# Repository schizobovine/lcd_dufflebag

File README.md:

lcd_dufflebag
=============

Variation on the common LCD "backpack" design. Instead of using an IO expander or full blown ATMega, however, this design uses an ATTiny84 to drive the LCD, with just enough pins left over to be an I2C slave. Can control RGB LCDs via an optional WS2811 chip or monochrome displays via a simple BJT.

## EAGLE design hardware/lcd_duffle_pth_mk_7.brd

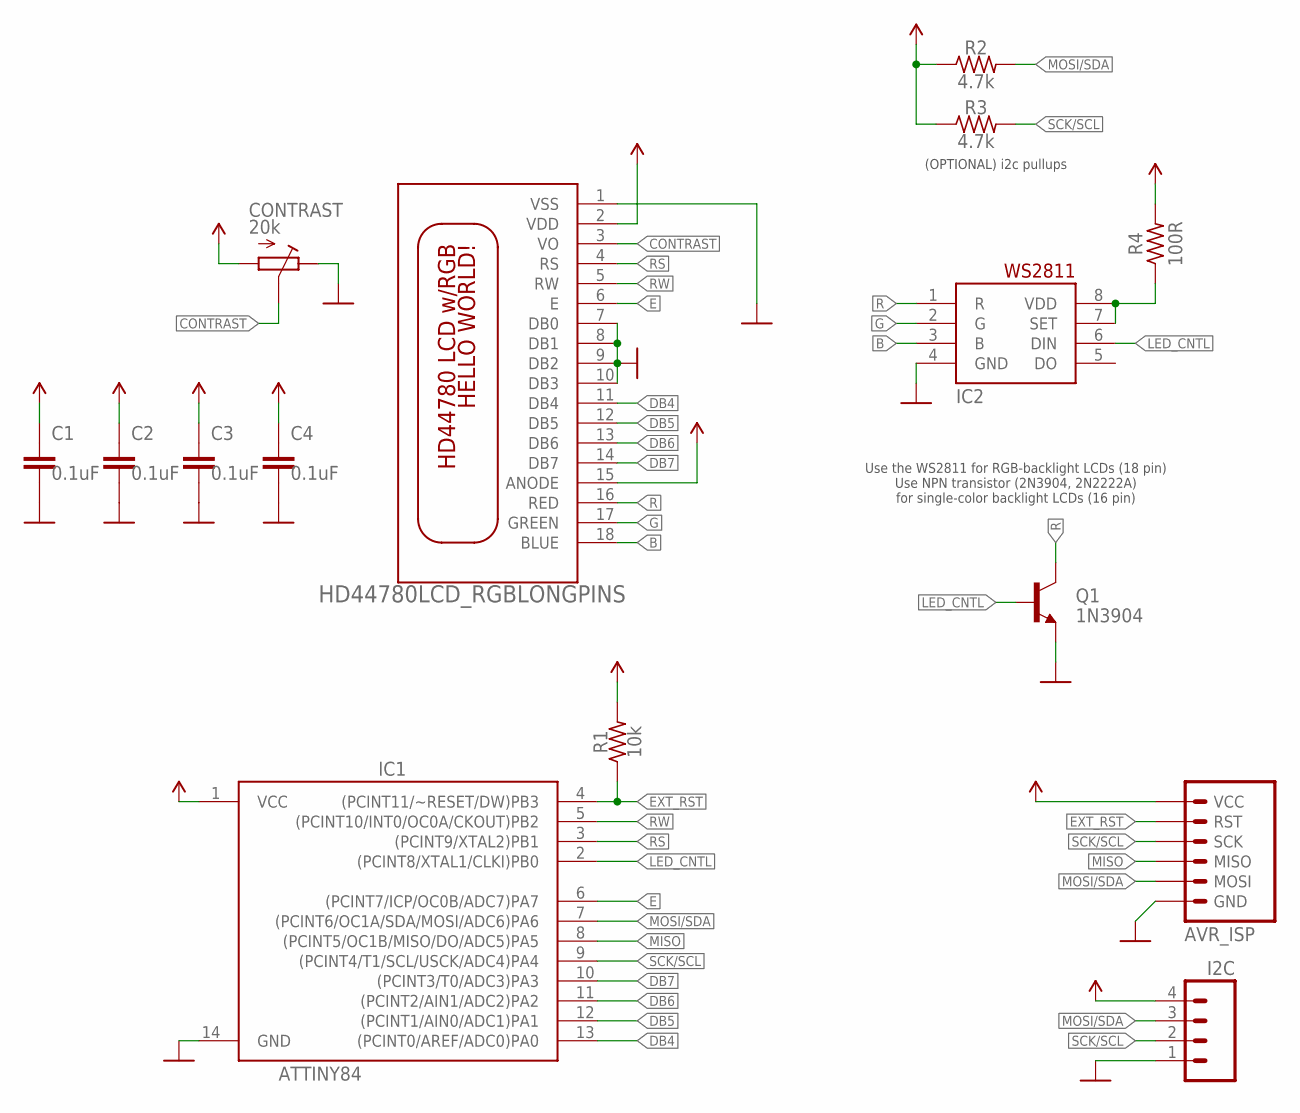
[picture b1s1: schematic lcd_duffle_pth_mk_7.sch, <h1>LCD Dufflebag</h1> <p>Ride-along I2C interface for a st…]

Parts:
AVR_ISP: AVR_MINI_PROGJST-XH-RA-PTH; AVR_MINI_PROG_JST_XH_RA
C1, C2, C3, C4: 0.1uF; C025-024X044
CONTRAST: 20k; POT-THUMBWHEEL
I2C: M04JST_XH_RA; JST-4-XH-RA-PTH
IC1: ATTINY84; DIL14
IC2: WS2811; SO08-SKINNYPADS
Q1: 1N3904; TO-92-AMMO
R1: 10k; RESISTOR-AXIAL-PTH-5.08MM
R2, R3: 4.7k; RESISTOR-AXIAL-PTH-5.08MM
R4: 100R; RESISTOR-AXIAL-PTH-5.08MM
U$1: HD44780LCD_RGBLONGPINS; LCD1602-RGB-CENTERED

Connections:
5V: AVR_ISP.2 (VCC), C1.2, C2.2, C3.2, C4.2, CONTRAST.1 (A), I2C.4, IC1.1 (VCC), R1.P$2 (2), R2.P$1 (1), R3.P$1 (1), R4.P$2 (2), U$1.2 (VDD), U$1.15 (ANODE)
B: IC2.3 (B), U$1.18 (BLUE)
CONTRAST: CONTRAST.2 (S), CONTRAST.2@1 (S), U$1.3 (VO)
DB4: IC1.13 ((PCINT0/AREF/ADC0)PA0), U$1.11 (DB4)
DB5: IC1.12 ((PCINT1/AIN0/ADC1)PA1), U$1.12 (DB5)
DB6: IC1.11 ((PCINT2/AIN1/ADC2)PA2), U$1.13 (DB6)
DB7: IC1.10 ((PCINT3/T0/ADC3)PA3), U$1.14 (DB7)
E: IC1.6 ((PCINT7/ICP/OC0B/ADC7)PA7), U$1.6 (E)
EXT_RST: AVR_ISP.5 (RST), IC1.4 ((PCINT11/~RESET/DW)PB3), R1.P$1 (1)
G: IC2.2 (G), U$1.17 (GREEN)
GND: AVR_ISP.6 (GND), C1.1, C2.1, C3.1, C4.1, CONTRAST.3 (E), I2C.1, IC1.14 (GND), IC2.4 (GND), Q1.1 (E), U$1.1 (VSS), U$1.7 (DB0), U$1.8 (DB1), U$1.9 (DB2), U$1.10 (DB3)
LED_CNTL: IC1.2 ((PCINT8/XTAL1/CLKI)PB0), IC2.6 (DIN), Q1.2 (B)
MISO: AVR_ISP.1 (MISO), IC1.8 ((PCINT5/OC1B/MISO/DO/ADC5)PA5)
MOSI/SDA: AVR_ISP.4 (MOSI), I2C.3, IC1.7 ((PCINT6/OC1A/SDA/MOSI/ADC6)PA6), R2.P$2 (2)
unnamed: IC2.7 (SET), IC2.8 (VDD), R4.P$1 (1)
R: IC2.1 (R), Q1.3 (C), U$1.16 (RED)
RS: IC1.3 ((PCINT9/XTAL2)PB1), U$1.4 (RS)
RW: IC1.5 ((PCINT10/INT0/OC0A/CKOUT)PB2), U$1.5 (RW)
SCK/SCL: AVR_ISP.3 (SCK), I2C.2, IC1.9 ((PCINT4/T1/SCL/USCK/ADC4)PA4), R3.P$2 (2)

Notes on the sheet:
Use the WS2811 for RGB-backlight LCDs (18 pin) Use NPN transistor (2N3904, 2N2222A) for single-color backlight LCDs (16 pin)
(OPTIONAL) i2c pullups

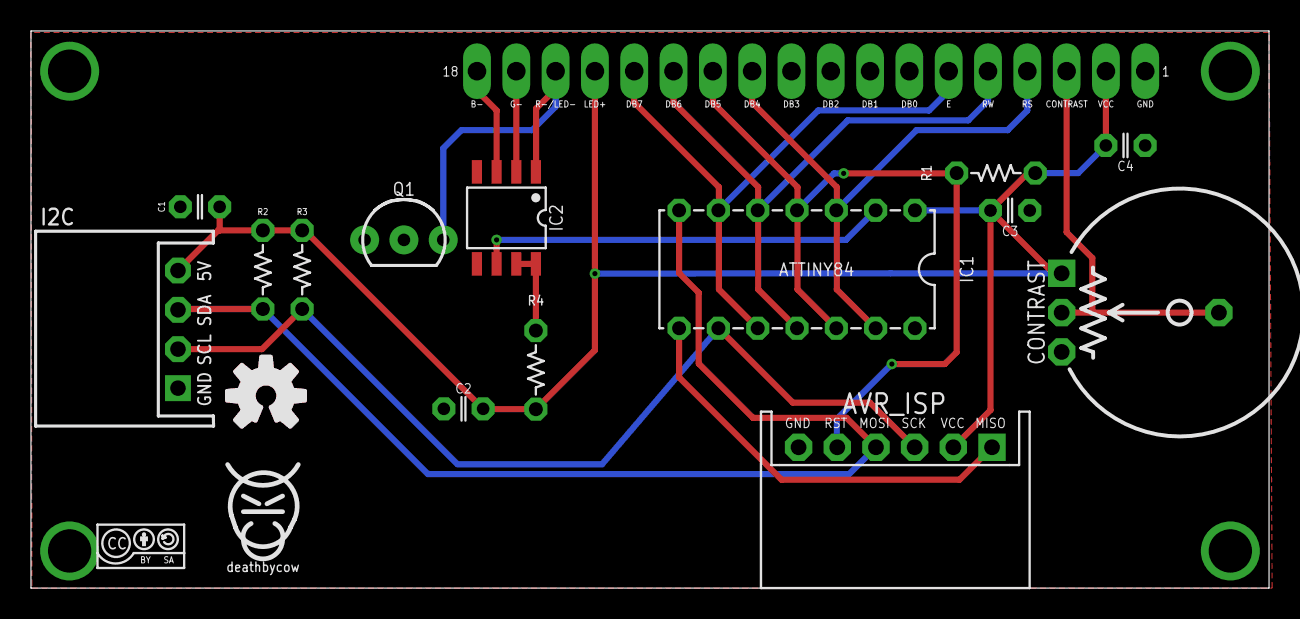
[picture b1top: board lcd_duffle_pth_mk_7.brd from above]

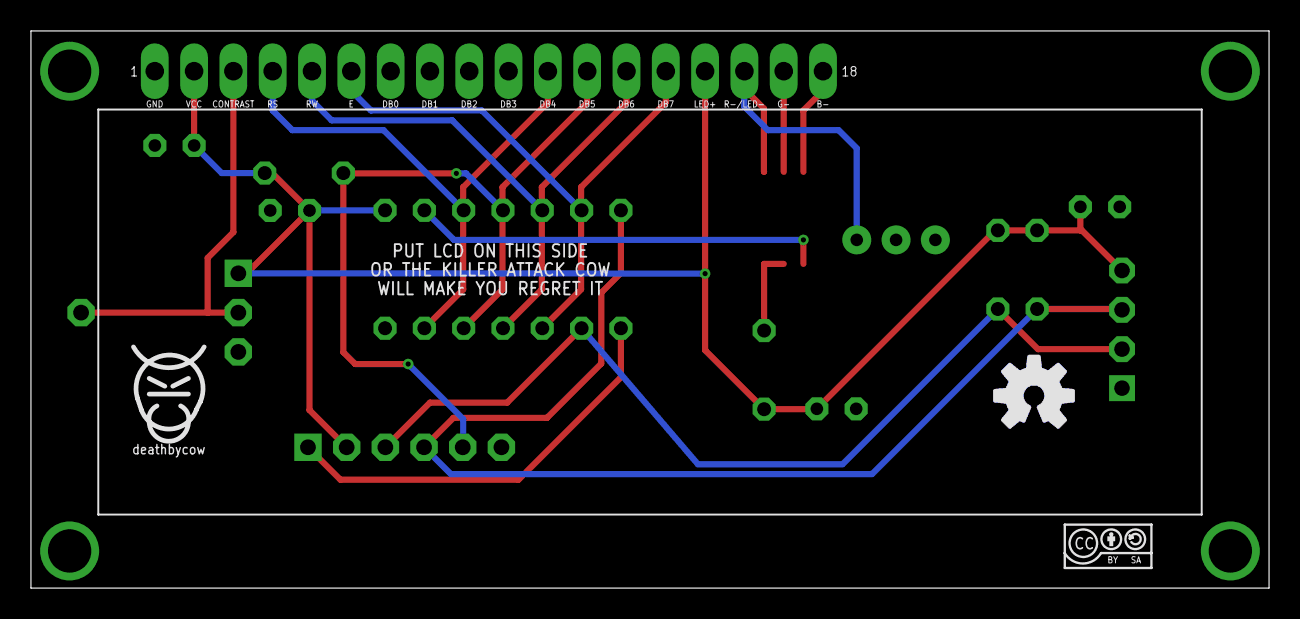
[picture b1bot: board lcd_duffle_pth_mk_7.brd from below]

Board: 2 copper layers, 80.0 x 36.0 mm, 21 parts (5 on the bottom side), 19 nets.

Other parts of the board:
U$2, U$3: COW_SMALL
U$4, U$6: CC-BY-SA-4.0-NO-URL
U$5: OSHWLOGO_TOP_0.2_A
U$7: OSHWLOGO_BOT_0.2_A

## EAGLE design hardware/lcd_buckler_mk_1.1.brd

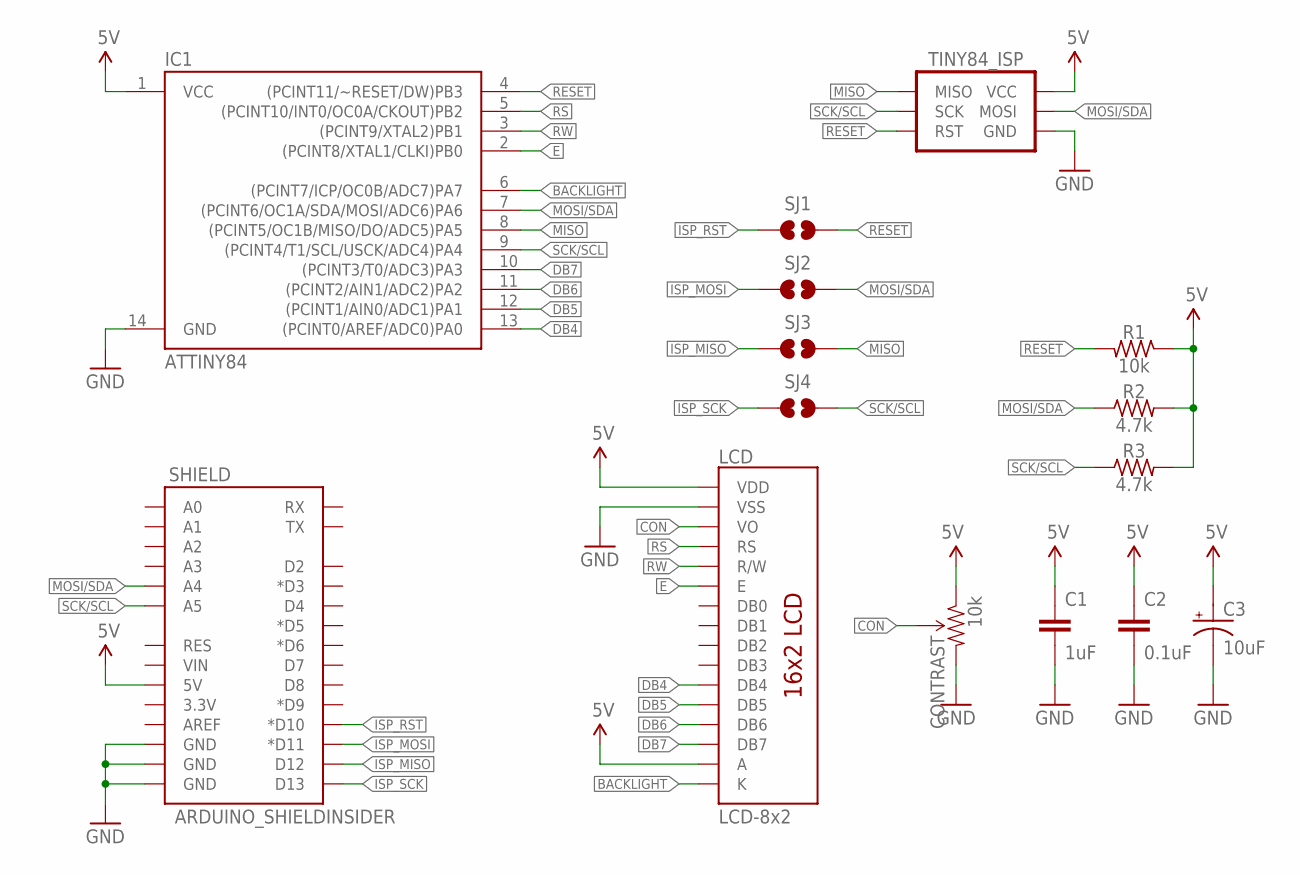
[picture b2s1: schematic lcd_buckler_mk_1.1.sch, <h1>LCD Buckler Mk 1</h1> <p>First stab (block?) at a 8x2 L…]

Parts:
C1: 1uF; C025-024X044
C2: 0.1uF; C025-024X044
C3: 10uF; E2,5-5
CONTRAST: 10k; TRIM_POT_PTH
IC1: ATTINY84; DIL14
LCD: LCD-8x2; LCD-8X2
R1: 10k; RESISTOR-AXIAL-PTH-7.62MM
R2, R3: 4.7k; RESISTOR-AXIAL-PTH-7.62MM
SHIELD: ARDUINO_SHIELDINSIDER; ARDUINO_SHIELD_NOOUTLINE_INSIDE
SJ1, SJ2, SJ3, SJ4: JUMPER-PAD-2-NO; PAD-JUMPER-2-NO_NO_SILK
TINY84_ISP: AVR_SPI_PRG_6PTH; 2X3

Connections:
5V: C1.1, C2.1, C3.+, CONTRAST.1 (CCW), IC1.1 (VCC), LCD.2 (VDD), LCD.15 (A), R1.P$1 (1), R2.P$2 (2), R3.P$2 (2), SHIELD.5V, TINY84_ISP.2 (VCC)
BACKLIGHT: IC1.6 ((PCINT7/ICP/OC0B/ADC7)PA7), LCD.16 (K)
CON: CONTRAST.2 (WIPER), LCD.3 (VO)
DB4: IC1.13 ((PCINT0/AREF/ADC0)PA0), LCD.11 (DB4)
DB5: IC1.12 ((PCINT1/AIN0/ADC1)PA1), LCD.12 (DB5)
DB6: IC1.11 ((PCINT2/AIN1/ADC2)PA2), LCD.13 (DB6)
DB7: IC1.10 ((PCINT3/T0/ADC3)PA3), LCD.14 (DB7)
E: IC1.2 ((PCINT8/XTAL1/CLKI)PB0), LCD.6 (E)
GND: C1.2, C2.2, C3.-, CONTRAST.3 (CW), IC1.14 (GND), LCD.1 (VSS), SHIELD.GND@0 (GND), SHIELD.GND@1 (GND), SHIELD.GND@2 (GND), TINY84_ISP.6 (GND)
ISP_MISO: SHIELD.D12, SJ3.1
ISP_MOSI: SHIELD.D11 (*D11), SJ2.1
ISP_RST: SHIELD.D10 (*D10), SJ1.1
ISP_SCK: SHIELD.D13, SJ4.1
MISO: IC1.8 ((PCINT5/OC1B/MISO/DO/ADC5)PA5), SJ3.2, TINY84_ISP.1 (MISO)
MOSI/SDA: IC1.7 ((PCINT6/OC1A/SDA/MOSI/ADC6)PA6), R2.P$1 (1), SHIELD.A4, SJ2.2, TINY84_ISP.4 (MOSI)
RESET: IC1.4 ((PCINT11/~RESET/DW)PB3), R1.P$2 (2), SJ1.2, TINY84_ISP.5 (RST)
RS: IC1.5 ((PCINT10/INT0/OC0A/CKOUT)PB2), LCD.4 (RS)
RW: IC1.3 ((PCINT9/XTAL2)PB1), LCD.5 (R/W)
SCK/SCL: IC1.9 ((PCINT4/T1/SCL/USCK/ADC4)PA4), R3.P$1 (1), SHIELD.A5, SJ4.2, TINY84_ISP.3 (SCK)

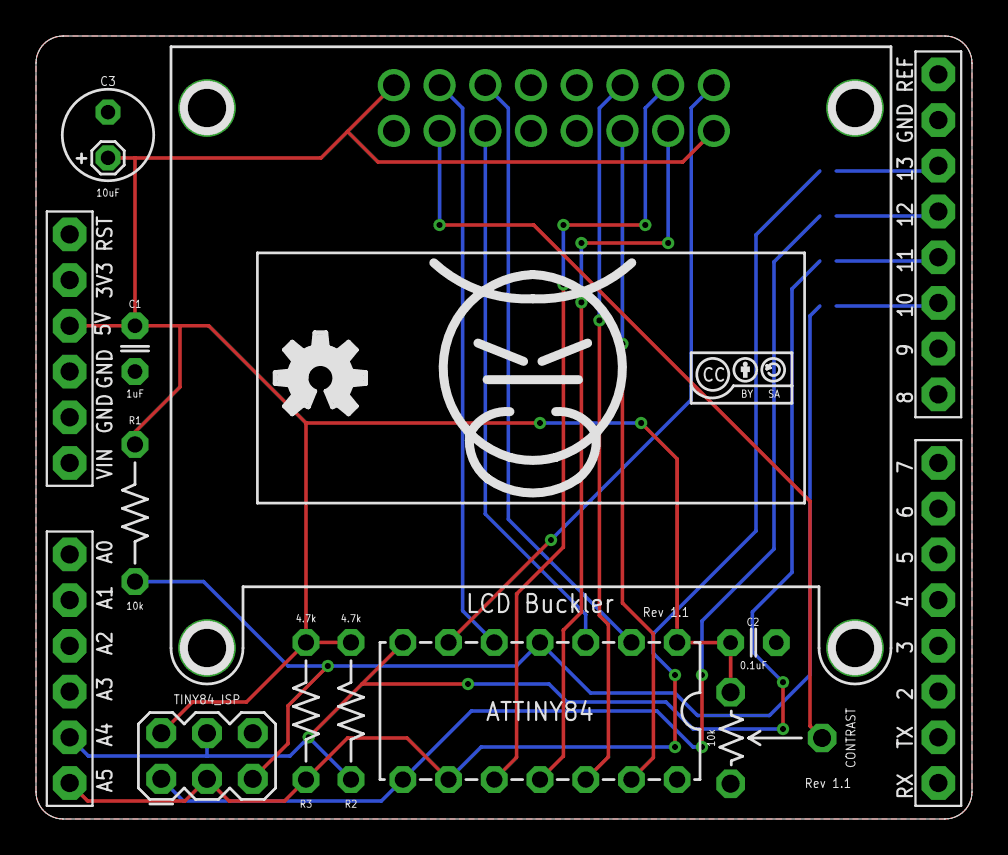
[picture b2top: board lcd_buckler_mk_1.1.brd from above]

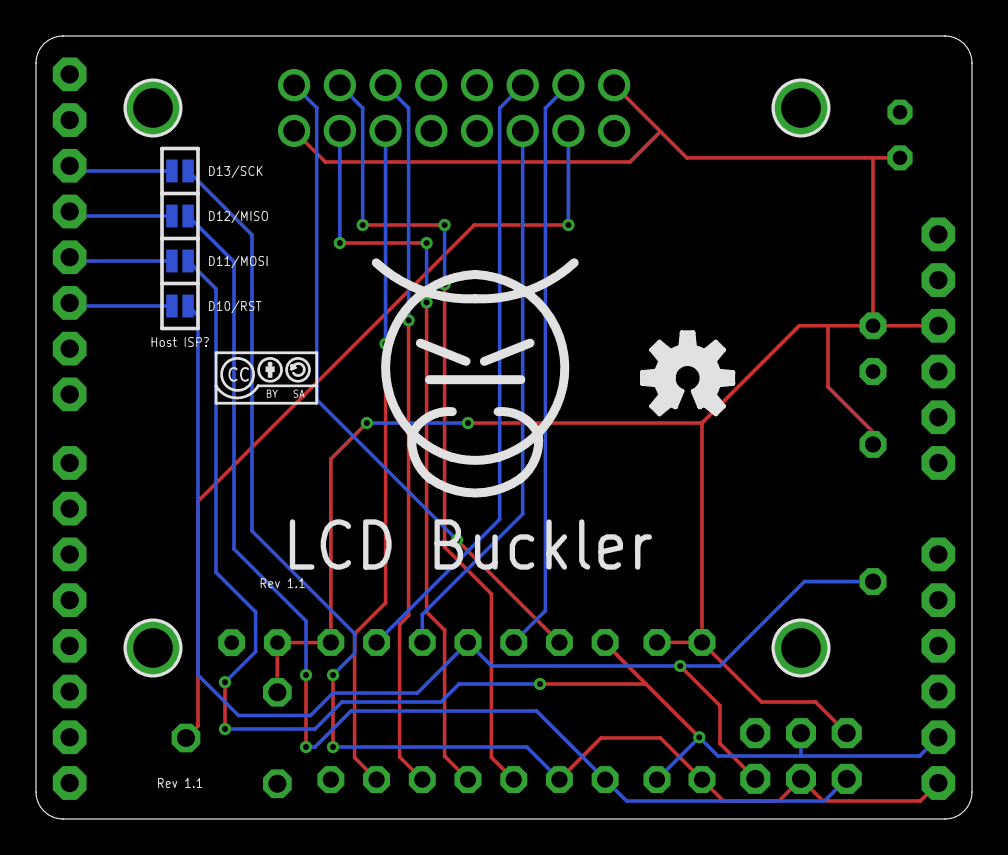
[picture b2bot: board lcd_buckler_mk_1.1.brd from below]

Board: 2 copper layers, 52.0 x 43.5 mm, 21 parts (7 on the bottom side), 19 nets.

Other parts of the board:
U$1, U$2: COW
U$3, U$4: CC-BY-SA-4.0-NO-URL
U$5, U$6: OSHWLOGO_SILKONLY

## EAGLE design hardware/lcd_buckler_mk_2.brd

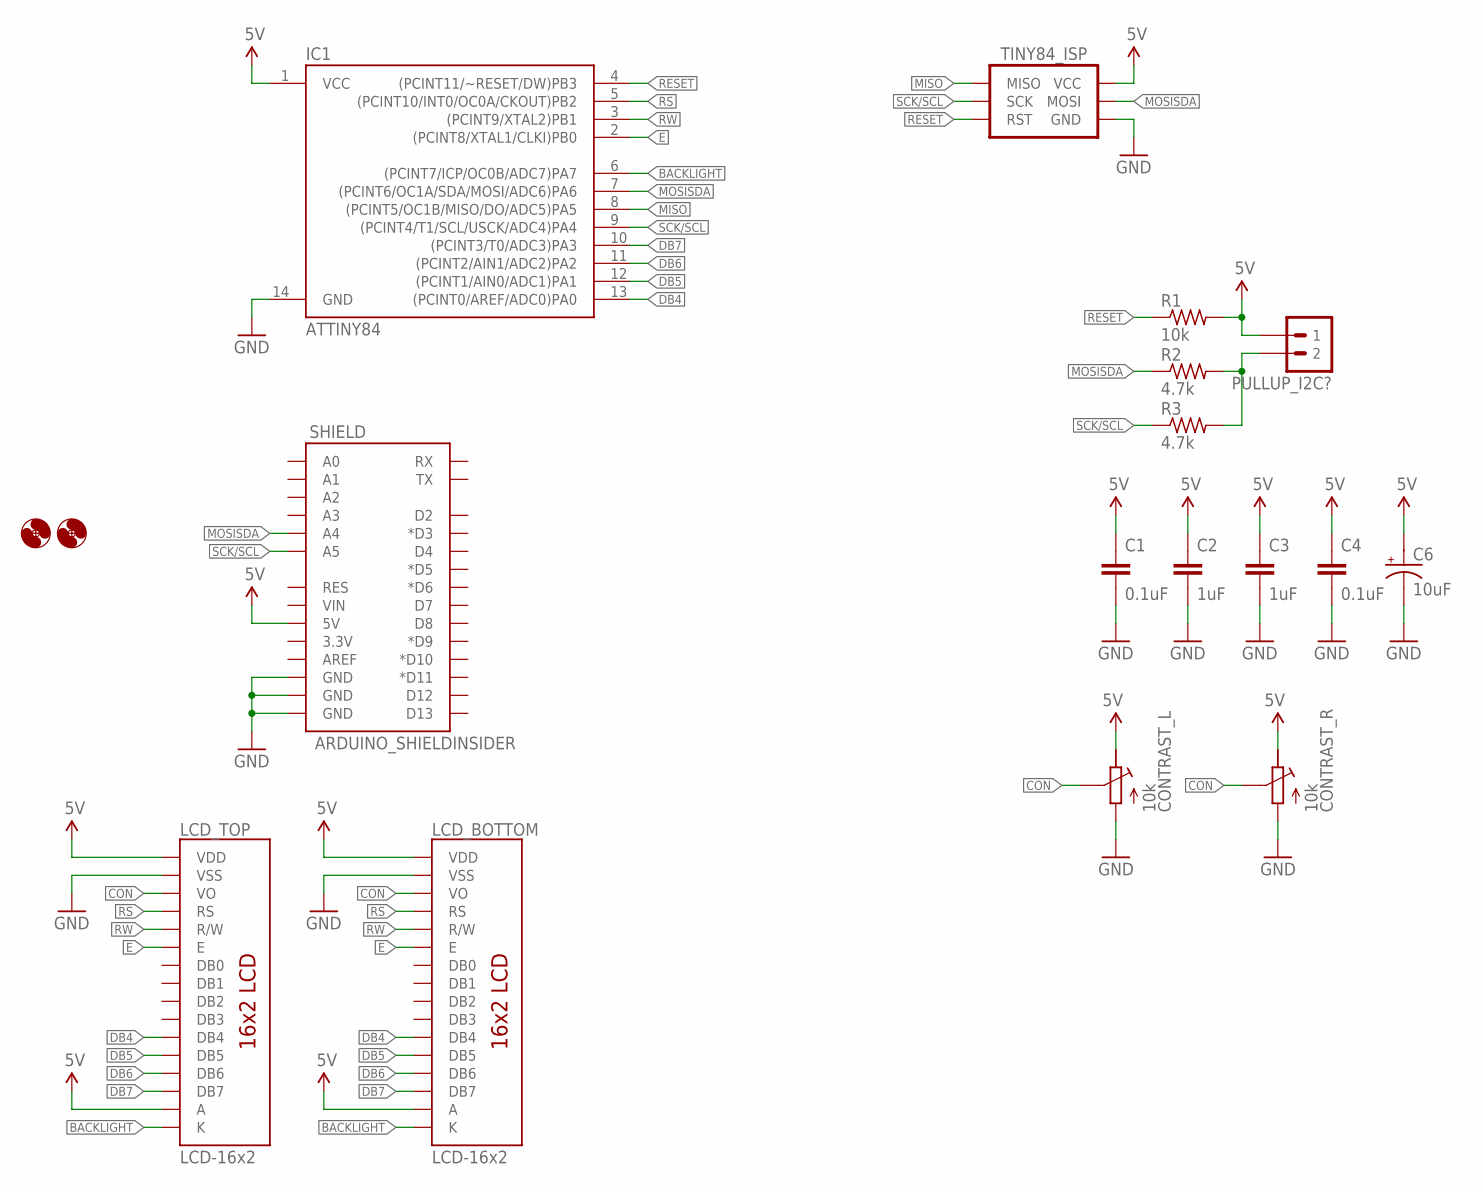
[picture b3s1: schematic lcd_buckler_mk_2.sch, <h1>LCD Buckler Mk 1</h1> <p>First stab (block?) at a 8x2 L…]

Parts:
C1: 0.1uF; C0805
C2, C3: 1uF; C025-024X044
C4: 0.1uF; C025-024X044
C6: 10uF; E2,5-5
CONTRAST_L: 10k; POT-THUMBWHEEL
CONTRAST_R: 10k; POT-THUMBWHEEL
H1, H2: HOLE#2; HOLE-#2
IC1: ATTINY84; SO14
LCD_BOTTOM: LCD-16x2; LCD-16X2-PINS-ONLY
LCD_TOP: LCD-16x2; LCD-16X2-PINS-ONLY
PULLUP_I2C?: M02PTH; 1X02
R1: 10k; R0805
R2, R3: 4.7k; RESISTOR-AXIAL-PTH-7.68MM
SHIELD: ARDUINO_SHIELDINSIDER; ARDUINO_SHIELD_NOOUTLINE_INSIDE
TINY84_ISP: AVR_SPI_PRG_6PTH; 2X3

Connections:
5V: C1.1, C2.1, C3.1, C4.1, C6.+, CONTRAST_L.3 (E), CONTRAST_R.3 (E), IC1.1 (VCC), LCD_BOTTOM.2 (VDD), LCD_BOTTOM.15 (A), LCD_TOP.2 (VDD), LCD_TOP.15 (A), PULLUP_I2C?.1, R1.2, SHIELD.5V, TINY84_ISP.2 (VCC)
BACKLIGHT: IC1.6 ((PCINT7/ICP/OC0B/ADC7)PA7), LCD_BOTTOM.16 (K), LCD_TOP.16 (K)
CON: CONTRAST_L.2 (S), CONTRAST_L.2@1 (S), CONTRAST_R.2 (S), CONTRAST_R.2@1 (S), LCD_BOTTOM.3 (VO), LCD_TOP.3 (VO)
DB4: IC1.13 ((PCINT0/AREF/ADC0)PA0), LCD_BOTTOM.11 (DB4), LCD_TOP.11 (DB4)
DB5: IC1.12 ((PCINT1/AIN0/ADC1)PA1), LCD_BOTTOM.12 (DB5), LCD_TOP.12 (DB5)
DB6: IC1.11 ((PCINT2/AIN1/ADC2)PA2), LCD_BOTTOM.13 (DB6), LCD_TOP.13 (DB6)
DB7: IC1.10 ((PCINT3/T0/ADC3)PA3), LCD_BOTTOM.14 (DB7), LCD_TOP.14 (DB7)
E: IC1.2 ((PCINT8/XTAL1/CLKI)PB0), LCD_BOTTOM.6 (E), LCD_TOP.6 (E)
GND: C1.2, C2.2, C3.2, C4.2, C6.-, CONTRAST_L.1 (A), CONTRAST_R.1 (A), IC1.14 (GND), LCD_BOTTOM.1 (VSS), LCD_TOP.1 (VSS), SHIELD.GND@0 (GND), SHIELD.GND@1 (GND), SHIELD.GND@2 (GND), TINY84_ISP.6 (GND)
MISO: IC1.8 ((PCINT5/OC1B/MISO/DO/ADC5)PA5), TINY84_ISP.1 (MISO)
MOSISDA: IC1.7 ((PCINT6/OC1A/SDA/MOSI/ADC6)PA6), R2.P$1 (1), SHIELD.A4, TINY84_ISP.4 (MOSI)
unnamed: PULLUP_I2C?.2, R2.P$2 (2), R3.P$2 (2)
RESET: IC1.4 ((PCINT11/~RESET/DW)PB3), R1.1, TINY84_ISP.5 (RST)
RS: IC1.5 ((PCINT10/INT0/OC0A/CKOUT)PB2), LCD_BOTTOM.4 (RS), LCD_TOP.4 (RS)
RW: IC1.3 ((PCINT9/XTAL2)PB1), LCD_BOTTOM.5 (R/W), LCD_TOP.5 (R/W)
SCK/SCL: IC1.9 ((PCINT4/T1/SCL/USCK/ADC4)PA4), R3.P$1 (1), SHIELD.A5, TINY84_ISP.3 (SCK)

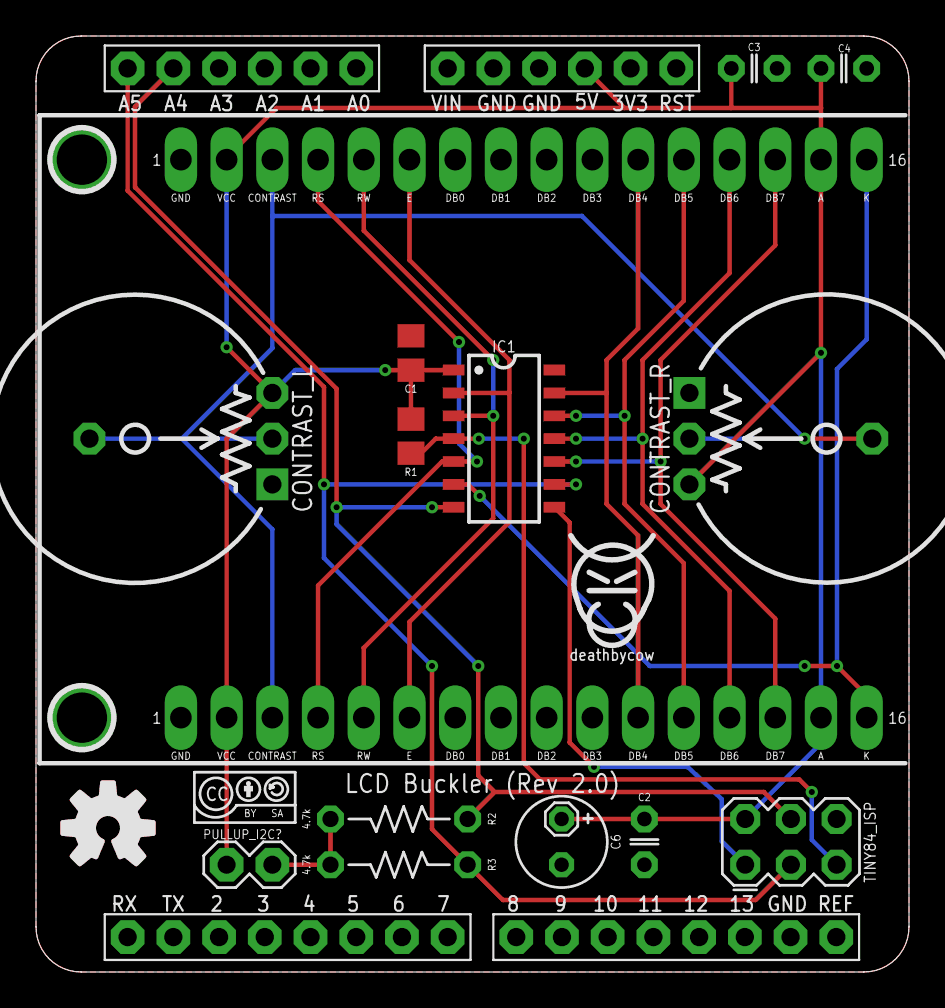
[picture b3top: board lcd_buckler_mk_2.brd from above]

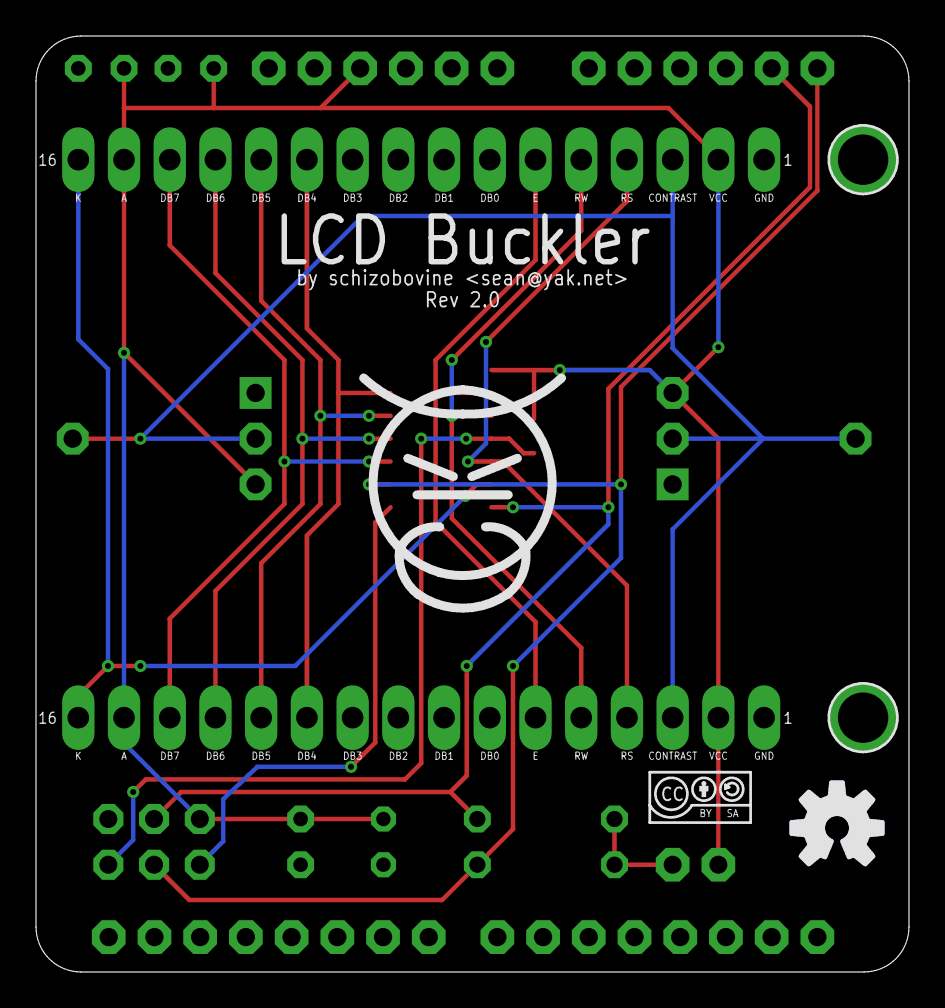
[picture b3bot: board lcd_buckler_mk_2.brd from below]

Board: 2 copper layers, 48.5 x 52.0 mm, 24 parts (2 on the bottom side), 16 nets.

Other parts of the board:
U$1: COW
U$2: COW_SMALL
U$3, U$4: CC-BY-SA-4.0-NO-URL
U$5: OSHWLOGO_TOP_0.2_A
U$6: OSHWLOGO_BOT_0.2_A

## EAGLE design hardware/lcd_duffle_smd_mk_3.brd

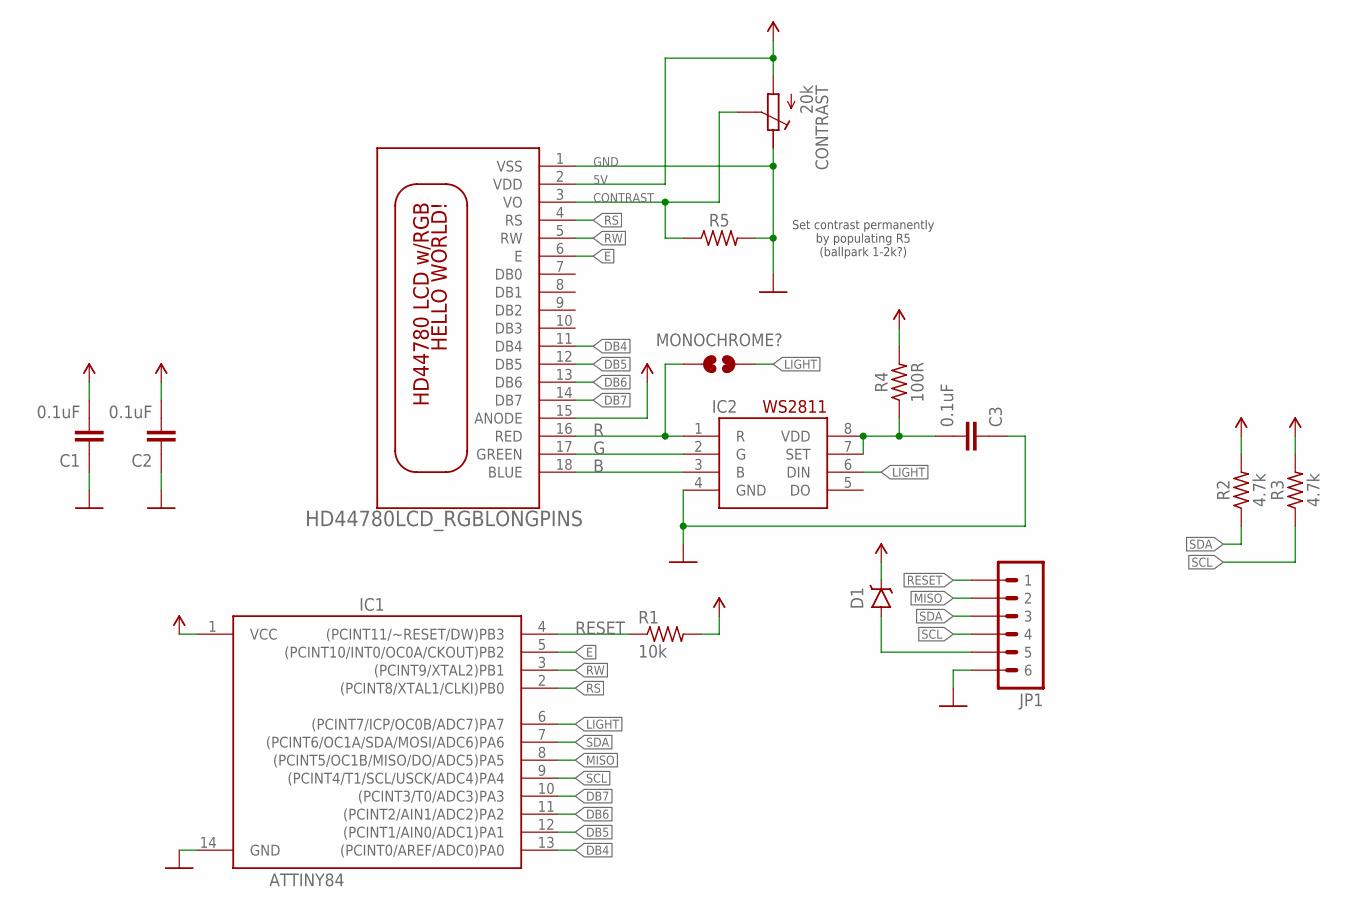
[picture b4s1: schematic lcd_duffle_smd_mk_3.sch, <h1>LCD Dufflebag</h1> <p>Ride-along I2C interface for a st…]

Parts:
C1, C2, C3: 0.1uF; C0805
CONTRAST: 20k; RTRIM3314Z-SIDE
D1: MBRA140; SMA-DIODE
IC1: ATTINY84; SO14
IC2: WS2811; SO08-SKINNYPADS
JP1: M06SMD; 1X06-SMD
MONOCHROME?: JUMPER-PAD-2-NOYES_SILK; PAD-JUMPER-2-NO_YES_SILK
R1: 10k; R0805
R2, R3: 4.7k; R0805
R4: 100R; R0805
R5: RESISTORR0805; R0805
U$1: HD44780LCD_RGBLONGPINS; LCD1602-RGB-CENTERED

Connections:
5V: C1.2, C2.2, CONTRAST.1 (A), D1.C, IC1.1 (VCC), R1.2, R2.2, R3.2, R4.2, U$1.2 (VDD), U$1.15 (ANODE)
B: IC2.3 (B), U$1.18 (BLUE)
CONTRAST: CONTRAST.2 (S), R5.1, U$1.3 (VO)
DB4: IC1.13 ((PCINT0/AREF/ADC0)PA0), U$1.11 (DB4)
DB5: IC1.12 ((PCINT1/AIN0/ADC1)PA1), U$1.12 (DB5)
DB6: IC1.11 ((PCINT2/AIN1/ADC2)PA2), U$1.13 (DB6)
DB7: IC1.10 ((PCINT3/T0/ADC3)PA3), U$1.14 (DB7)
E: IC1.5 ((PCINT10/INT0/OC0A/CKOUT)PB2), U$1.6 (E)
G: IC2.2 (G), U$1.17 (GREEN)
GND: C1.1, C2.1, C3.1, CONTRAST.3 (E), IC1.14 (GND), IC2.4 (GND), JP1.6, R5.2, U$1.1 (VSS)
LIGHT: IC1.6 ((PCINT7/ICP/OC0B/ADC7)PA7), IC2.6 (DIN), MONOCHROME?.2
MISO: IC1.8 ((PCINT5/OC1B/MISO/DO/ADC5)PA5), JP1.2
unnamed: D1.A, JP1.5
unnamed: C3.2, IC2.7 (SET), IC2.8 (VDD), R4.1
R: IC2.1 (R), MONOCHROME?.1, U$1.16 (RED)
RESET: IC1.4 ((PCINT11/~RESET/DW)PB3), JP1.1, R1.1
RS: IC1.2 ((PCINT8/XTAL1/CLKI)PB0), U$1.4 (RS)
RW: IC1.3 ((PCINT9/XTAL2)PB1), U$1.5 (RW)
SCL: IC1.9 ((PCINT4/T1/SCL/USCK/ADC4)PA4), JP1.4, R3.1
SDA: IC1.7 ((PCINT6/OC1A/SDA/MOSI/ADC6)PA6), JP1.3, R2.1

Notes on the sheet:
Set contrast permanently by populating R5 (ballpark 1-2k?)

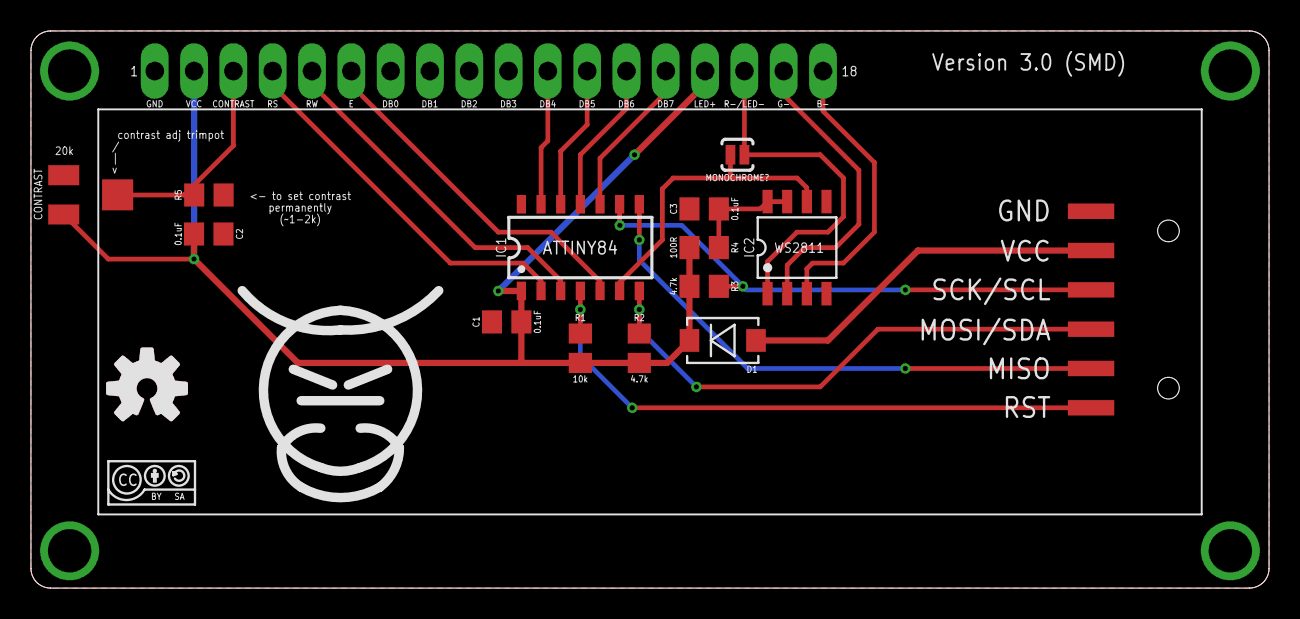
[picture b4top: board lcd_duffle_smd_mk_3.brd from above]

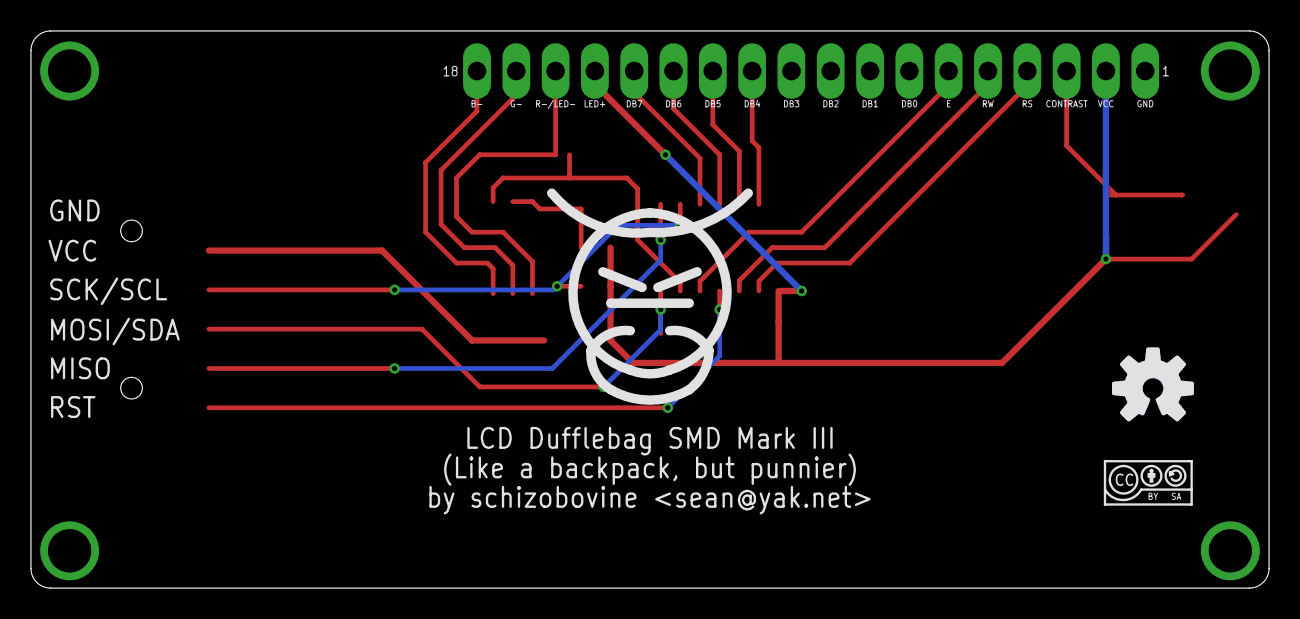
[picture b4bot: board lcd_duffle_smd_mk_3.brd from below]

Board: 2 copper layers, 80.0 x 36.0 mm, 21 parts (2 on the bottom side), 20 nets.

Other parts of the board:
U$2, U$3: COW
U$4, U$5: CC-BY-SA-4.0-NO-URL
U$6: OSHWLOGO_TOP_0.2_A
U$7: OSHWLOGO_BOT_0.2_A

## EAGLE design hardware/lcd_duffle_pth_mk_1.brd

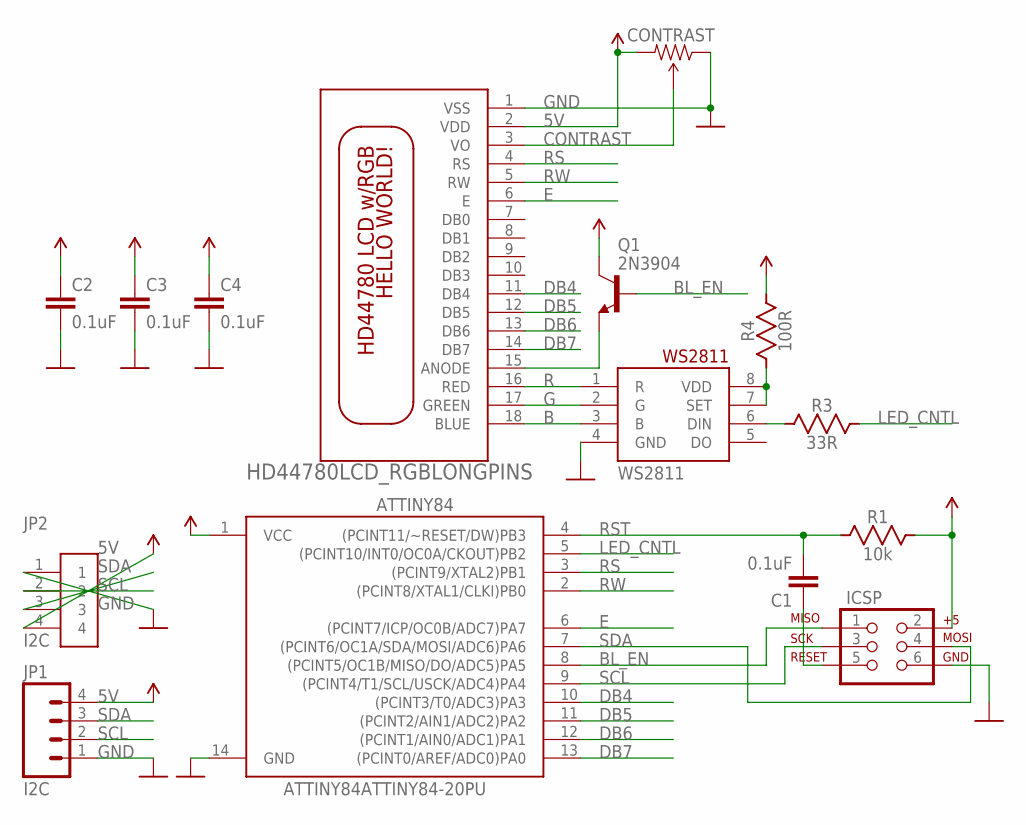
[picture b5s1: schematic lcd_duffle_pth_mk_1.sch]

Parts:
ATTINY84: ATTINY84ATTINY84-20PU; DIL14
C1, C2, C3, C4: 0.1uF; C025-024X044
CONTRAST: TRIMPOT3362U-2; 3362U-2
ICSP: AVR_SPI_PRG_6PTH; 2X3
JP1: I2C; MOLEX-1X4
JP2: I2C; 1X04-BIG
Q1: 2N3904; TO-92-AMMO
R1: 10k; AXIAL-PTH-5.08MM
R3: 33R; AXIAL-PTH-5.08MM
R4: 100R; AXIAL-PTH-5.08MM
U$1: HD44780LCD_RGBLONGPINS; LCD1602-RGB
WS2811: WS2811-SOP8; SO08-SKINNYPADS

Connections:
5V: ATTINY84.1 (VCC), C2.2, C3.2, C4.2, CONTRAST.3 (CW), ICSP.2, JP1.4, JP2.4, Q1.3 (C), R1.P$1 (2), R4.P$1 (2), U$1.2 (VDD)
B: U$1.18 (BLUE), WS2811.3 (B)
BL_EN: ATTINY84.8 ((PCINT5/OC1B/MISO/DO/ADC5)PA5), ICSP.1, Q1.2 (B)
CONTRAST: CONTRAST.2 (WIPER), U$1.3 (VO)
DB4: ATTINY84.10 ((PCINT3/T0/ADC3)PA3), U$1.11 (DB4)
DB5: ATTINY84.11 ((PCINT2/AIN1/ADC2)PA2), U$1.12 (DB5)
DB6: ATTINY84.12 ((PCINT1/AIN0/ADC1)PA1), U$1.13 (DB6)
DB7: ATTINY84.13 ((PCINT0/AREF/ADC0)PA0), U$1.14 (DB7)
E: ATTINY84.6 ((PCINT7/ICP/OC0B/ADC7)PA7), U$1.6 (E)
G: U$1.17 (GREEN), WS2811.2 (G)
GND: ATTINY84.14 (GND), C2.1, C3.1, C4.1, CONTRAST.1 (CCW), ICSP.6, JP1.1, JP2.1, U$1.1 (VSS), WS2811.4 (GND)
LED_CNTL: ATTINY84.5 ((PCINT10/INT0/OC0A/CKOUT)PB2), R3.P$1 (2)
unnamed: R3.P$2 (1), WS2811.6 (DIN)
unnamed: R4.P$2 (1), WS2811.7 (SET), WS2811.8 (VDD)
unnamed: C1.1, ICSP.5
unnamed: Q1.1 (E), U$1.15 (ANODE)
R: U$1.16 (RED), WS2811.1 (R)
RS: ATTINY84.3 ((PCINT9/XTAL2)PB1), U$1.4 (RS)
RST: ATTINY84.4 ((PCINT11/~RESET/DW)PB3), C1.2, R1.P$2 (1)
RW: ATTINY84.2 ((PCINT8/XTAL1/CLKI)PB0), U$1.5 (RW)
SCL: ATTINY84.9 ((PCINT4/T1/SCL/USCK/ADC4)PA4), ICSP.3, JP1.2, JP2.2
SDA: ATTINY84.7 ((PCINT6/OC1A/SDA/MOSI/ADC6)PA6), ICSP.4, JP1.3, JP2.3

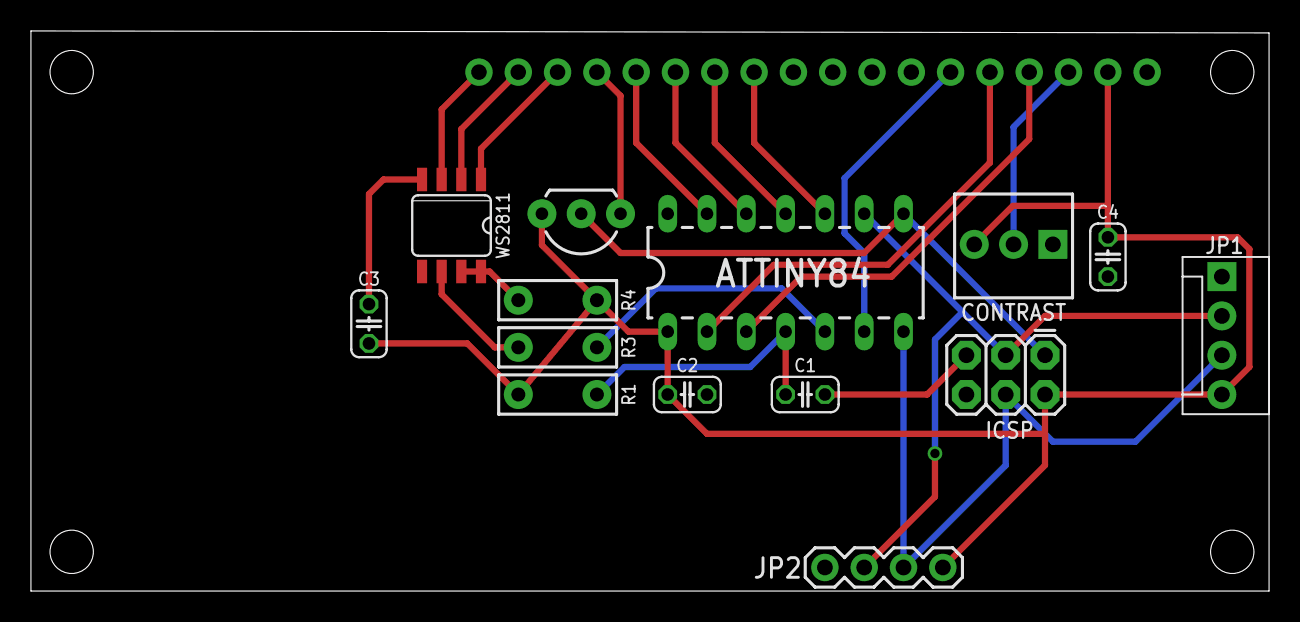
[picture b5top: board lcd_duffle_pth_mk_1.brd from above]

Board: 2 copper layers, 80.0 x 36.2 mm, 15 parts (1 on the bottom side), 22 nets.

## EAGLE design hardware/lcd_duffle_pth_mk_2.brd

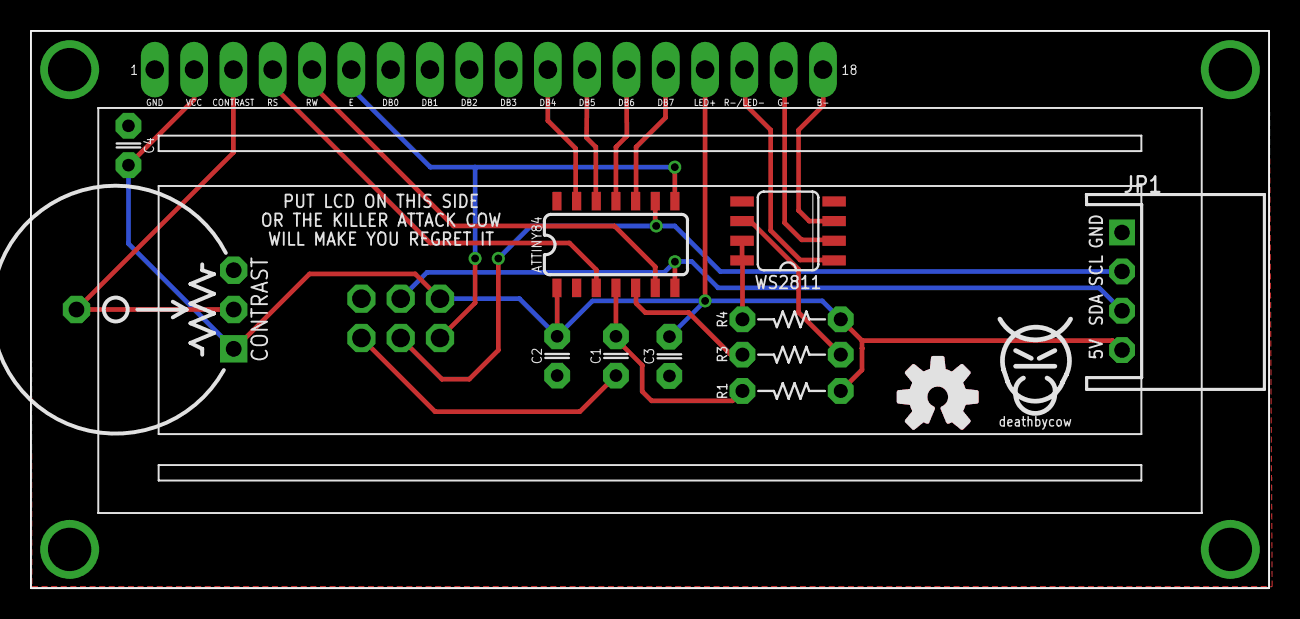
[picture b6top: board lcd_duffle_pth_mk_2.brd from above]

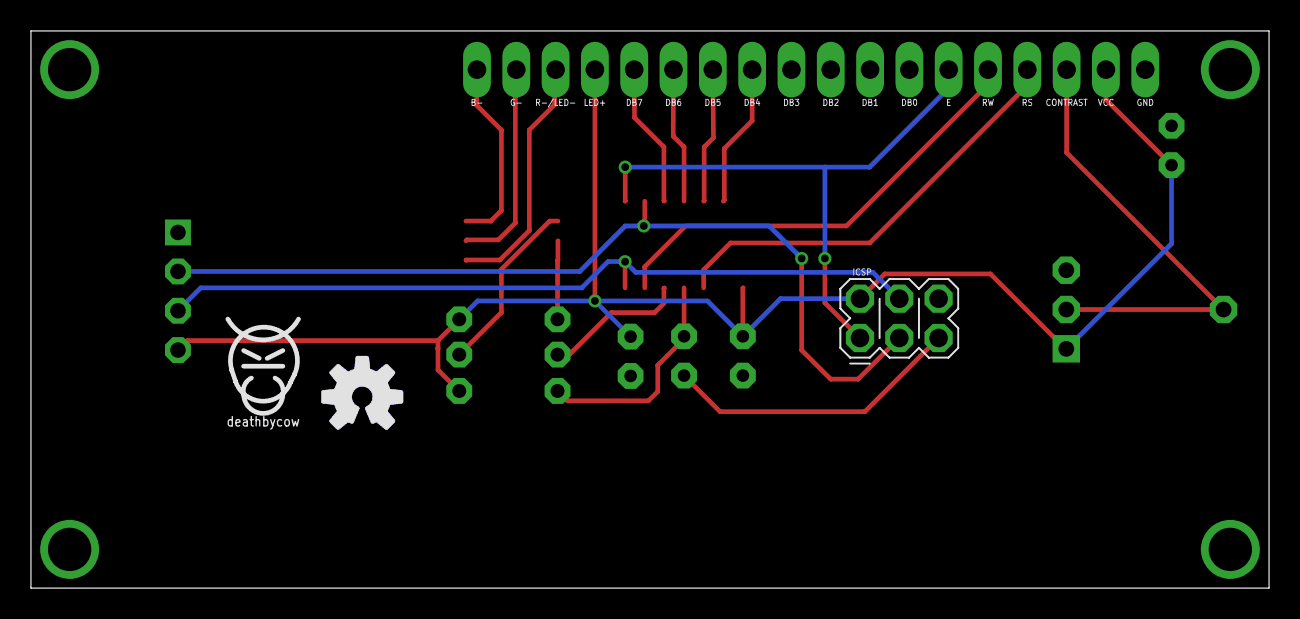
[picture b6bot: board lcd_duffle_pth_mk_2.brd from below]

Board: 2 copper layers, 80.0 x 36.0 mm, 17 parts (4 on the bottom side), 20 nets.

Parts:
ATTINY84: ATTINY84; SO14
C1, C2, C3, C4: 0.1uF; C025-024X044
CONTRAST: POT-THUMBWHEEL
ICSP: 2X3_POGO
JP1: I2C; 1X04-2.5MM_JST_XH_RA
R1: 10k; RESISTOR-AXIAL-PTH-5.08MM
R3: 33R; RESISTOR-AXIAL-PTH-5.08MM
R4: 100R; RESISTOR-AXIAL-PTH-5.08MM
U$1: HD44780LCD_RGBLONGPINS; LCD1602-RGB-CENTERED
U$2, U$3: COW_SMALL
U$5: OSHWLOGO_TOP_0.2_A
U$7: OSHWLOGO_BOT_0.2_A
WS2811: WS2811-SOP8; SO08-SKINNYPADS

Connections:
5V: ATTINY84.1, C2.2, C3.2, C4.2, CONTRAST.1, ICSP.P$2, JP1.4, R1.P$2, R4.P$2, U$1.2, U$1.15
B: U$1.18, WS2811.3
CONTRAST: CONTRAST.2, CONTRAST.2@1, U$1.3
DB4: ATTINY84.13, U$1.11
DB5: ATTINY84.12, U$1.12
DB6: ATTINY84.11, U$1.13
DB7: ATTINY84.10, U$1.14
E: ATTINY84.8, ICSP.P$1, U$1.6
G: U$1.17, WS2811.2
GND: ATTINY84.14, C2.1, C3.1, C4.1, CONTRAST.3, ICSP.P$6, JP1.1, U$1.1, U$1.7, U$1.8, U$1.9, U$1.10, WS2811.4
LED_CNTL: ATTINY84.5, R3.P$2
unnamed: R3.P$1, WS2811.6
unnamed: R4.P$1, WS2811.7, WS2811.8
unnamed: C1.1, ICSP.P$5
R: U$1.16, WS2811.1
RS: ATTINY84.3, U$1.4
RST: ATTINY84.4, C1.2, R1.P$1
RW: ATTINY84.6, U$1.5
SCL: ATTINY84.9, ICSP.P$3, JP1.2
SDA: ATTINY84.7, ICSP.P$4, JP1.3

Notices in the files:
parts and their libraries:
SparkFun-DigitalIC: Licensing: Creative Commons ShareAlike 4.0 International - https://creativecommons.org/licenses/by-sa/4.0
